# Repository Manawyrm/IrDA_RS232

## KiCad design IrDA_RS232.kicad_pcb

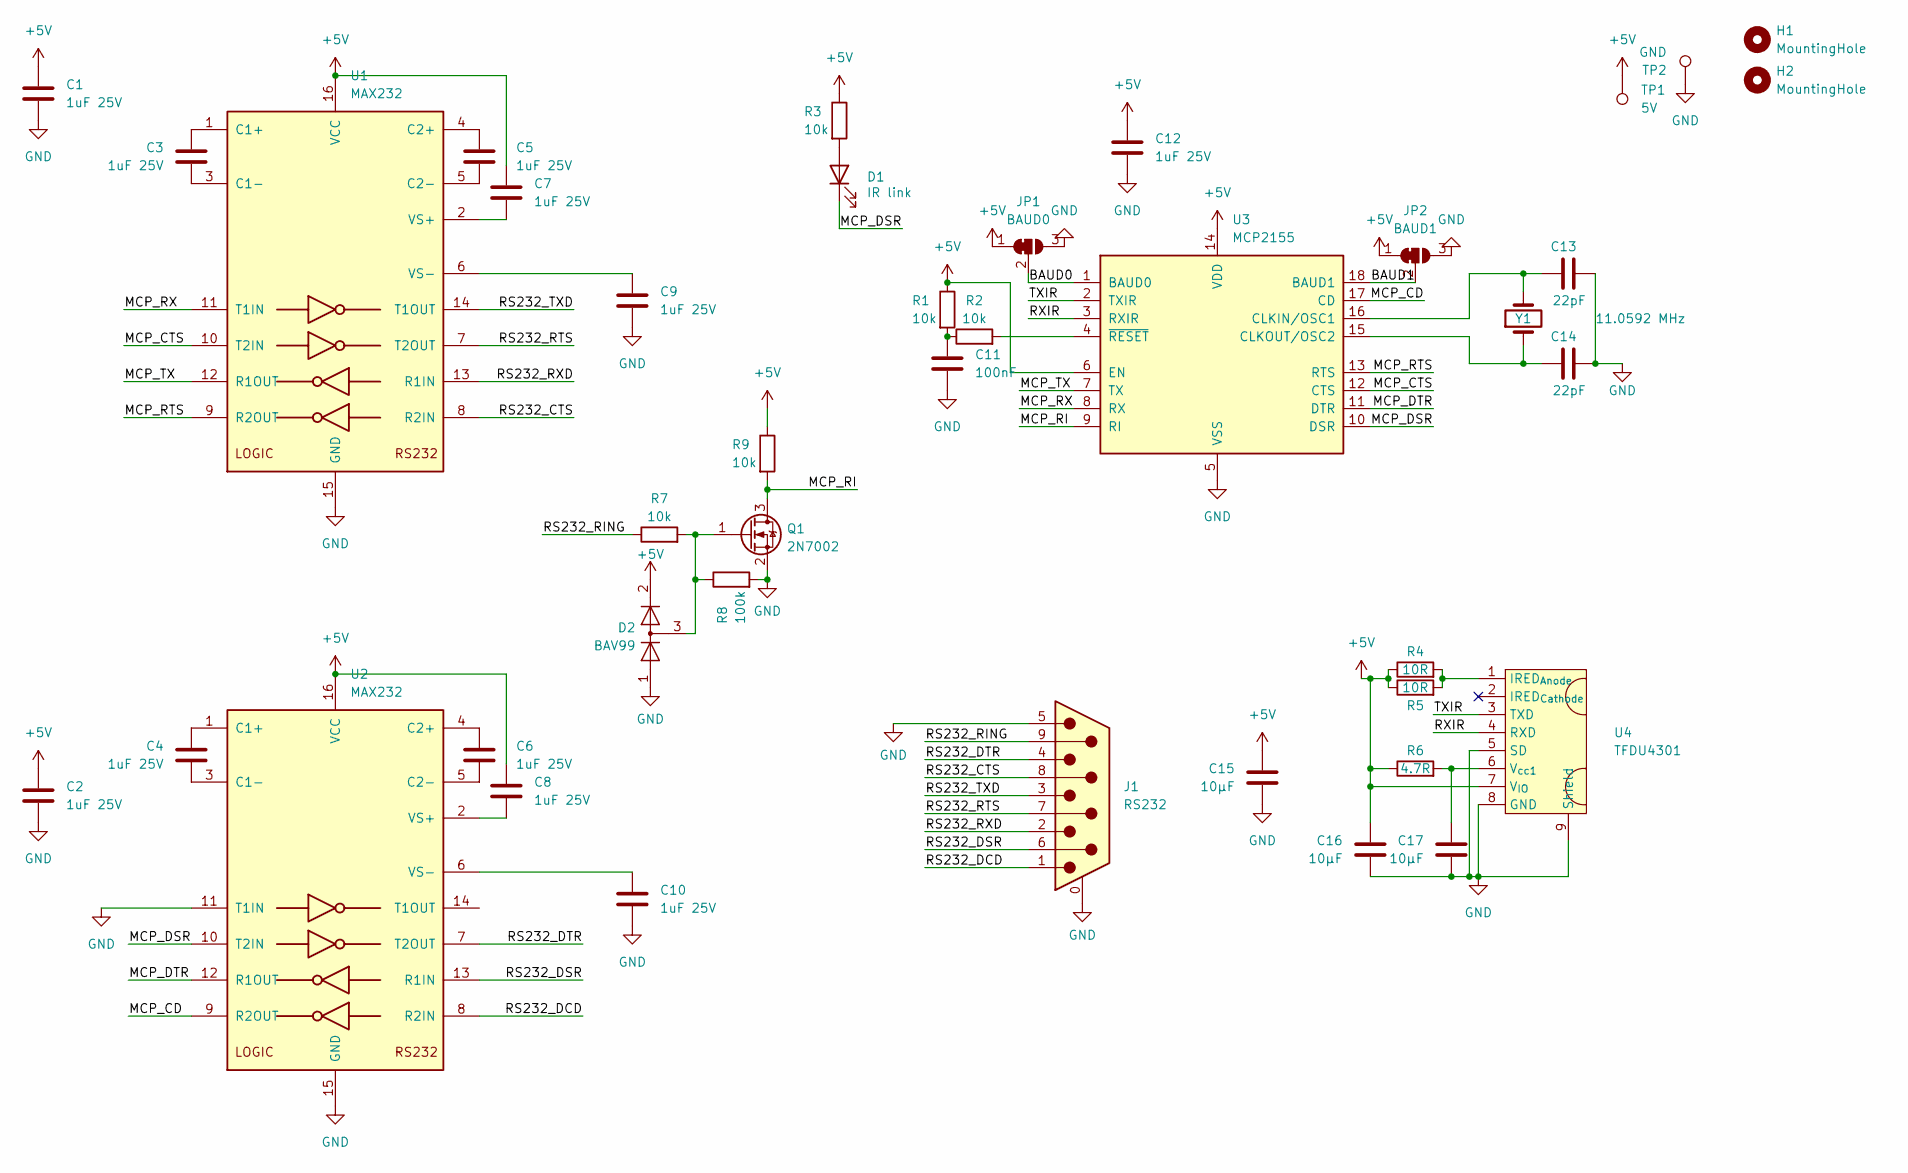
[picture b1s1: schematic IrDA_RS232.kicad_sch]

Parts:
C1, C2, C3, C4, C5, C6, C7, C8, C9, C10, C12: 1uF 25V; C_0402_1005Metric; LCSC C52923
C11: 100nF; C_0402_1005Metric; LCSC C1525
C13, C14: 22pF; C_0402_1005Metric; LCSC C1555
C15, C16, C17: 10µF; C_0603_1608Metric; LCSC C19702
D1: IR link; LED_0603_1608Metric; LCSC C72043
D2: BAV99; SOT-23; LCSC C2500
H1, H2: MountingHole; ToolingHole_JLCSMT
J1: RS232; DSUB-9_Male_Vertical_P2.77x2.84mm_MountingHoles
JP1: BAUD0; SolderJumper-3_P1.3mm_Bridged12_Pad1.0x1.5mm
JP2: BAUD1; SolderJumper-3_P1.3mm_Bridged12_Pad1.0x1.5mm
Q1: 2N7002; SOT-23; LCSC C8545
R1, R2, R3, R7, R9: 10k; R_0402_1005Metric; LCSC C25744
R4, R5: 10R; R_1206_3216Metric; LCSC C17903
R6: 4.7R; R_0805_2012Metric; LCSC C17675
R8: 100k; R_0402_1005Metric; LCSC C25741
TP1: 5V; TestPoint_Pad_2.0x2.0mm
TP2: GND; TestPoint_Pad_2.0x2.0mm
U1, U2: MAX232; SOIC-16_3.9x9.9mm_P1.27mm; LCSC C26860
U3: MCP2155; SOIC-18W_7.5x11.6mm_P1.27mm
U4: TFDU4301
Y1: 11.0592 MHz; Crystal_SMD_5032-2Pin_5.0x3.2mm; LCSC C112574

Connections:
+5V: C1.1, C2.1, C7.2, C8.2, C12.1, C15.2, C16.2, D2.2 (A), JP1.1 (A), JP2.1 (A), R1.1, R3.1, R4.1, R5.1, R6.1, R9.1, TP1.1, U1.16 (VCC), U2.16 (VCC), U3.6 (EN), U3.14 (VDD), U4.7 (V_{IO})
/BAUD0: JP1.2 (C), U3.1 (BAUD0)
/BAUD1: JP2.2 (C), U3.18 (BAUD1)
/MCP_CD: U2.9 (R2OUT), U3.17 (CD)
/MCP_CTS: U1.10 (T2IN), U3.12 (CTS)
/MCP_DSR: D1.1 (K), U2.10 (T2IN), U3.10 (DSR)
/MCP_DTR: U2.12 (R1OUT), U3.11 (DTR)
/MCP_RI: Q1.3 (D), R9.2, U3.9 (RI)
/MCP_RTS: U1.9 (R2OUT), U3.13 (RTS)
/MCP_RX: U1.11 (T1IN), U3.8 (RX)
/MCP_TX: U1.12 (R1OUT), U3.7 (TX)
/RS232_CTS: J1.8, U1.8 (R2IN)
/RS232_DCD: J1.1, U2.8 (R2IN)
/RS232_DSR: J1.6, U2.13 (R1IN)
/RS232_DTR: J1.4, U2.7 (T2OUT)
/RS232_RING: J1.9, R7.1
/RS232_RTS: J1.7, U1.7 (T2OUT)
/RS232_RXD: J1.2, U1.13 (R1IN)
/RS232_TXD: J1.3, U1.14 (T1OUT)
/RXIR: U3.3 (RXIR), U4.4 (RXD)
/TXIR: U3.2 (TXIR), U4.3 (TXD)
GND: C1.2, C2.2, C9.2, C10.2, C11.2, C12.2, C13.2, C14.2, C15.1, C16.1, C17.1, D2.1 (K), J1.0 (PAD), J1.5, JP1.3 (B), JP2.3 (B), Q1.2 (S), R8.2, TP2.1, U1.15 (GND), U2.11 (T1IN), U2.15 (GND), U3.5 (VSS), U4.5 (SD), U4.8 (GND), U4.9 (Shield)
unnamed: C3.1, U1.3 (C1-)
unnamed: C3.2, U1.1 (C1+)
unnamed: C4.1, U2.3 (C1-)
unnamed: C4.2, U2.1 (C1+)
unnamed: C5.1, U1.4 (C2+)
unnamed: C5.2, U1.5 (C2-)
unnamed: C6.1, U2.4 (C2+)
unnamed: C6.2, U2.5 (C2-)
unnamed: C7.1, U1.2 (VS+)
unnamed: C8.1, U2.2 (VS+)
unnamed: C9.1, U1.6 (VS-)
unnamed: C10.1, U2.6 (VS-)
unnamed: C11.1, R1.2, R2.1
unnamed: C13.1, U3.16 (CLKIN/OSC1), Y1.2
unnamed: C14.1, U3.15 (CLKOUT/OSC2), Y1.1
unnamed: C17.2, R6.2, U4.6 (V_{cc1})
unnamed: D1.2 (A), R3.2
unnamed: D2.3 (K), Q1.1 (G), R7.2, R8.1
unnamed: R2.2, U3.4 (~RESET)
unnamed: R4.2, R5.2, U4.1 (IRED_{Anode})

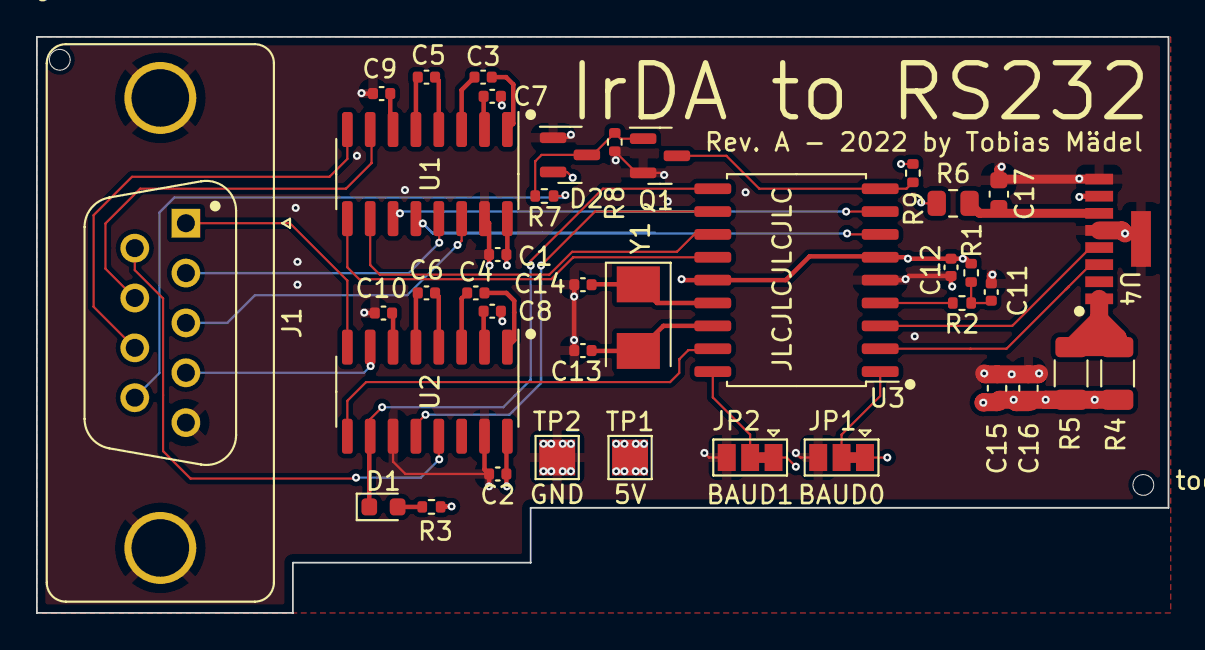
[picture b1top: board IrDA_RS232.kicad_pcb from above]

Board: 4 copper layers, 62.9 x 32.0 mm, 41 parts (0 on the bottom side), 42 nets.

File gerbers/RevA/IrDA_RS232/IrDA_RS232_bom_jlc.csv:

"Comment","Designator","Footprint","LCSC Part #"
"1uF 25V","C1,C2,C3,C4,C5,C6,C7,C8,C9,C10,C12","C_0402_1005Metric","C52923"
"100nF","C11","C_0402_1005Metric","C1525"
"22pF","C13,C14","C_0402_1005Metric","C1555"
"10µF","C15,C16,C17","C_0603_1608Metric","C19702"
"IR link","D1","LED_0603_1608Metric","C72043"
"BAV99","D2","SOT-23","C2500"
"2N7002","Q1","SOT-23","C8545"
"10k","R1,R2,R3,R7,R9","R_0402_1005Metric","C25744"
"10R","R4,R5","R_1206_3216Metric","C17903"
"4.7R","R6","R_0805_2012Metric","C17675"
"100k","R8","R_0402_1005Metric","C25741"
"MAX232","U1,U2","SOIC-16_3.9x9.9mm_P1.27mm","C26860"
" 11.0592 MHz","Y1","Crystal_SMD_5032-2Pin_5.0x3.2mm","C112574"

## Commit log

2022-03-20 Add MCP2155 symbol
2022-03-20 RevA
2022-03-20 Create LICENSE
2022-03-21 schematic: add ring indication level converter
2022-03-22 add gerbers and PDF
